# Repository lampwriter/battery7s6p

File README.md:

# 7S6P 18650 module: top and bottom bus boards (v1)

KiCad 9.0.2. The boards are generated by `gen.py` (pcbnew API). `build.sh` regenerates them, fills the zones, runs DRC and renders. `export.sh` writes the JLCPCB outputs to `fab/`.

## v1.1: 1 oz copper variant
`gen.py` reads `CU_OZ` (default 2). `CU_OZ=1 ./build_1oz.sh` builds the 1 oz boards into `top_1oz/` and `bot_1oz/`; `./export_1oz.sh` writes `fab_1oz/`. Order those with **1 oz outer copper** (2 layers, 1.6 mm, ENIG): `fab_1oz/battery7s6p_top_1oz_gerbers.zip` and `fab_1oz/battery7s6p_bot_1oz_gerbers.zip`.

On the 1 oz top board the XT90 moves 23 mm down (y=62 to y=85) so the N7 tail spans rows 0–3 and the neck can carry the current. Cell fuses are 2.0 mm wide on 1 oz (v1 is 1.0 mm on 2 oz), the same copper cross-section and the same blow current. Balance-tap fuses widen from 0.25 mm to 0.45 mm. Every high-current path stays at about 9 C rise or under at 30 A (`fuse_calc_1oz.txt`; the XT90 pad wrap is the warmest, about 9.4 C). The v1 2 oz boards and `fab/` outputs are unchanged.

## v1.2: pressure-contact clamp design
`gen.py` reads `V12` (default off). `V12=1 ./build_v12.sh` builds the boards into `top_v12/` and `bot_v12/`; `./export_v12.sh` writes `fab_v12/`. Order those with **1 oz copper, ENIG, 0.8 mm**: `fab_v12/battery7s6p_top_v12_gerbers.zip` and `fab_v12/battery7s6p_bot_v12_gerbers.zip`. v1 and v1.1 stay selectable (`V12` defaults off), and their gerber zips are unchanged.

Cells stand proud of lipless HDPE holders. The 0.8 mm board has routed slots that make one flexible island per cell, joined by 10 mm bridges, so a short cell can deflect on its own. The stack at each end is a backing plate, **1/8 in silicone foam (Rogers BISCO HT-800)**, then the PCB. Twelve M4 rods sit in equal-length spacer tubes, which set the foam compression at about **25 N per cell**.

`fab_v12/battery7s6p_v12_drill_template.dxf` (and the matching SVG) is the drill template for the holders and plates. Sort cells to **±0.1 mm**. Fit **Kapton rings** on every + end. On the first build, verify **under 15 mV per contact at 5 A**. Details are in `contact_design_v12.txt` and `calc_v12.txt`.

## Arrangement
- 7 columns (series groups G1 to G7) by 6 rows (6 parallel cells per group). Pitch is 20.25 mm and the cell array is 141.75 x 121.5 mm. Each board is 182.75 x 134.5 mm, which includes a 35 mm connector tab.
- Cell orientation alternates by column. Odd groups have + up and even groups have - up.
- Nodes N0 (pack -) to N7 (pack +):
  - The top board busses N1 (G1+/G2-), N3 (G3+/G4-), N5 (G5+/G6-) and N7 (G7+, pack +).
  - The bottom board busses N0 (G1-, pack -), N2, N4 and N6.
- Each board's cell side is its **B (bottom) layer**, and the connectors sit on the outer F side. The bottom board is designed as seen from below, so it's mirrored and its tab ends up under the G1 end.
- Because 7S is odd, pack - (N0) is on the bottom board and pack + is on the top board. N0 reaches the top board's XT90 through one **10 AWG jumper with crimped M5 ring lugs** (about 250 mm) between LUG1 on each board. Bolted, no solder.
- Bottom taps N0, N2, N4 and N6 reach the top board through a **4-pin JST-XH female-female straight cable** (bottom J1 to top J3).

## Holder
This design uses the common square interlocking 18650 bracket: 20.25 mm centre pitch, 18.3/18.5 mm bore, 21.7 mm single cell, about 9 mm thick, ABS+PC V0. It's sold as 1P/2P/3P snap-together pieces (source: chinabatterymachine.com/tmaxcn.com spec table). Buy the **20.25 mm pitch** version, not the 19.0, 19.2 or 19.5 mm variants.

## Mounting
- Ten M3 holes (3.2 mm) at interstitial points between cells, mirror-symmetric so the top and bottom boards line up. Clamp the stack with M3 threaded rod through the holder's corner gaps.
- Two more M3 holes in the tab.
- Check the actual holder before ordering. If its corner gaps can't pass M3 rod, move the holes in `gen.py`.

## Cell contacts (no welding, no solder on cells)
- Positive end: a 6 mm ENIG pad on the cell side, with 6 vias in the pad to the outer layer. Only that pad is positive copper on the cell side. Nothing else on the cell side is copper within the 18.5 mm cell circle, so the bare can shoulder can't short.
- Negative end: a 12 mm ENIG pad, solid into a cell-side pour. That pour exists only under negative-end columns, where the cans are the same net.
- Solder mask covers everything except the contact pads.
- **Fit a fish-paper insulating ring on every + end.** It's marked on the silkscreen.
- Order with **ENIG**, and with **via-in-pad (epoxy filled and capped)** if you want flat + pads.
- Contact pressure comes from clamping the two boards against the holder stack.
- A fully placed SMD contact from JLCPCB/LCSC wasn't found in time. The candidates are MYOUNG MY-18650-04-J (+, C19184125) and MY-18650-05-J (-, C19184124), but their current rating, footprint and SMT suitability are unverified. They're not in the BOM.

## Fusing (one fuse per cell, at its + end)
- Each + island connects to the outer bus pour through a **1.0 mm x about 3.5 mm** 2 oz trace, inside a 6.5 mm no-pour circle.
- Numbers from `fuse_calc.py` / `fuse_calc.txt`:
  - IPC-2221 (external layer, 2 oz): 5.4 A at 20 C rise and 7.3 A at 40 C rise. Normal duty is 30 A / 6 = 5 A per cell.
  - Onderdonk (adiabatic melt): about 20 A in 1 s, 64 A in 100 ms and 200 A in 10 ms.
  - An internally shorted cell is fed by its 5 neighbours (well over 100 A), so the link should open in milliseconds.
- Onderdonk ignores heat sinking. The short link and the mask make the real blow current higher, so bench-test one board with a current source before trusting it.
- Negative ends are not fused (one fuse per cell is enough). Change `FUSE_W` in `gen.py` to retune.

## Bus (30 A)
- 2 oz copper.
- Outer-layer pours span the whole node width (40 mm or more), and the cell-side pours are added under the negative columns.
- Stitching vias (0.5/0.9 mm) sit only in negative-end columns, so there's no positive copper on the cell side near the cans.
- The tab pours are on both layers and carry the XT90 current.

## Connectors (JLCPCB THT assembly, see `fab/*BOM*`, `fab/*CPL*`)
| Ref | Part | LCSC |
|---|---|---|
| Top J1 | AMASS XT90PW-M PCB male, right angle (pad 1 = PACK+ N7, pad 2 = PACK- N0) | C3040689 |
| Top J2 | JST B8B-XH-A balance: pin 1 = N0 (0 V), pin 2 = N1 ... pin 8 = N7 (7S+) | C157972 |
| Top J3 / Bottom J1 | JST B4B-XH-A, inter-board tap link N0/N2/N4/N6 | C144395 |
- Every balance tap has a 0.25 mm x 3 mm fuse link. That's about 2 A continuous, and it melts at about 16 A in 100 ms.
- On the top board, J2/J3 pin 1 is the separate net `N0_SENSE`. It's connected to N0 only through the bottom board and cable, which is intentional.

## Fab settings
- 2 layers, 1.6 mm, **2 oz outer copper**, ENIG, any mask colour.
- Upload `battery7s6p_top_gerbers.zip` and `battery7s6p_bot_gerbers.zip` as separate orders.
- The CPL coordinates are footprint origins (pin 1), not centroids. Check the part placement and rotation in JLCPCB's assembly preview.

## DRC
Rules: 0.2 mm track and clearance, 0.3 mm hole, 0.6 mm via, 0.4 mm copper-to-edge. Zone clearance is 0.5 mm. Results:
- 0 errors and 0 unconnected items.
- Remaining warnings are harmless:
  - "footprint library battery7s6p not configured": the cell contacts are script-generated footprints.
  - XT90 silk overhangs the edge, because the connector intentionally overhangs by 2.6 mm.

## Open items
- Check XT90 polarity against the housing. The XT90-S anti-spark version is a cable connector, so put the XT90-S on the mating harness side. The PCB part is the standard XT90PW.
- Revolectrix balance pin order is assumed to be standard JST-XH (pin 1 = pack -). Check it against your adapter board.
- There's no BMS or balancer in v1. Real-world fuse-blow testing is still to do.

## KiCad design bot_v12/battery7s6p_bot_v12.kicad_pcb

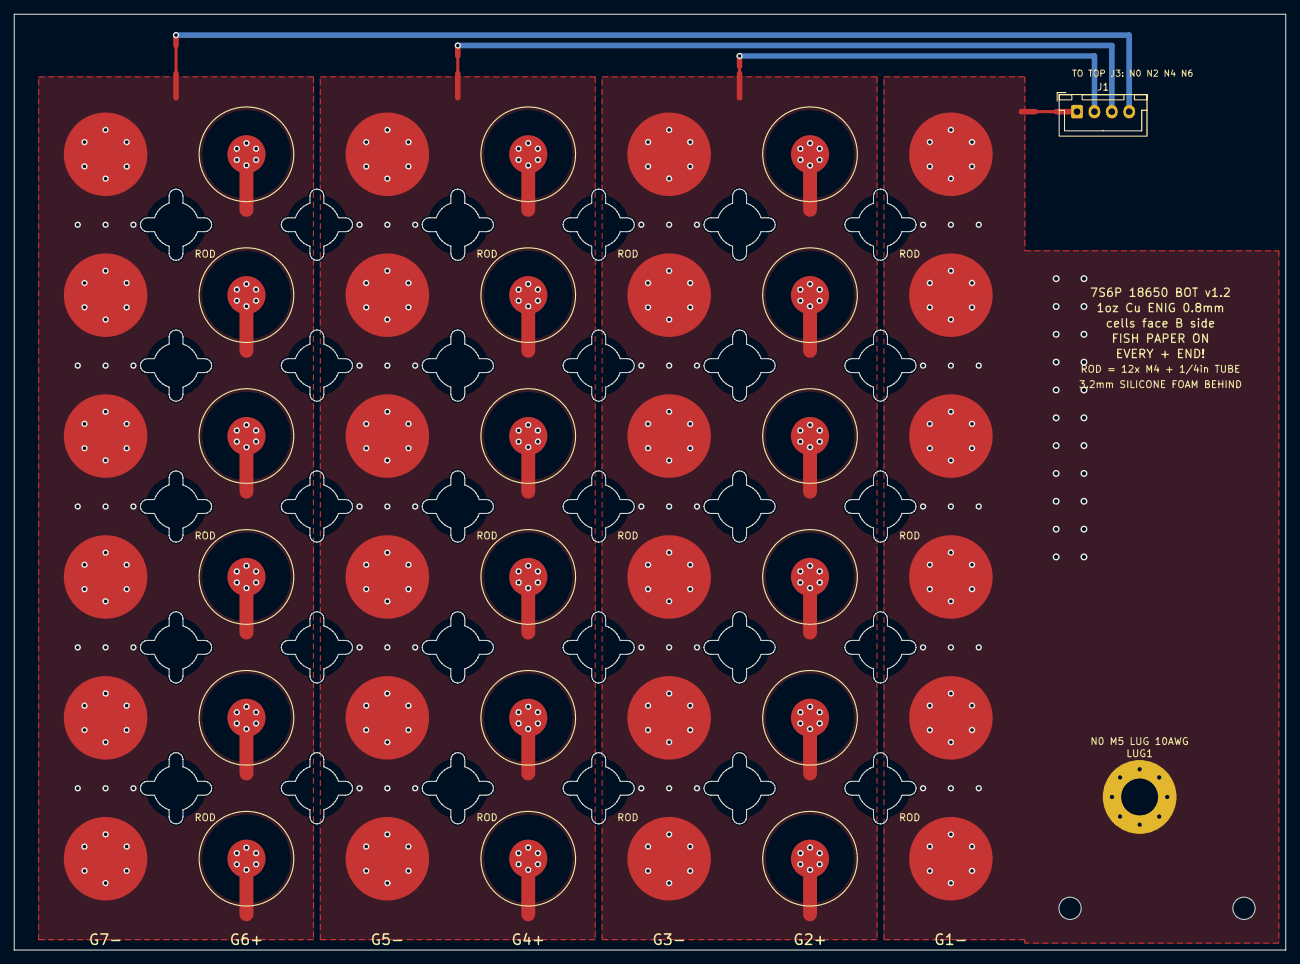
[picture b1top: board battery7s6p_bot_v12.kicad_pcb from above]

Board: 2 copper layers, 182.8 x 134.5 mm, 46 parts (0 on the bottom side), 4 nets.

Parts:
C1_1, C1_2, C1_3, C1_4, C1_5, C1_6, C3_1, C3_2, C3_3, C3_4, C3_5, C3_6, C5_1, C5_2, C5_3, C5_4, C5_5, C5_6, C7_1, C7_2, C7_3, C7_4, C7_5, C7_6: 18650_NEG; CELL_NEG_CONTACT
C2_1, C2_2, C2_3, C2_4, C2_5, C2_6, C4_1, C4_2, C4_3, C4_4, C4_5, C4_6, C6_1, C6_2, C6_3, C6_4, C6_5, C6_6: 18650_POS; CELL_POS_CONTACT
HT0, HT1: MountingHole_3.2mm_M3
J1: B4B-XH-A to TOP; JST_XH_B4B-XH-A_1x04_P2.50mm_Vertical
LUG1: N0 M5 LUG; MountingHole_5.3mm_M5_Pad_Via

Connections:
N0: C1_1.1, C1_2.1, C1_3.1, C1_4.1, C1_5.1, C1_6.1, J1.1, LUG1.1
N2: C2_1.1, C2_2.1, C2_3.1, C2_4.1, C2_5.1, C2_6.1, C3_1.1, C3_2.1, C3_3.1, C3_4.1, C3_5.1, C3_6.1, J1.2
N4: C4_1.1, C4_2.1, C4_3.1, C4_4.1, C4_5.1, C4_6.1, C5_1.1, C5_2.1, C5_3.1, C5_4.1, C5_5.1, C5_6.1, J1.3
N6: C6_1.1, C6_2.1, C6_3.1, C6_4.1, C6_5.1, C6_6.1, C7_1.1, C7_2.1, C7_3.1, C7_4.1, C7_5.1, C7_6.1, J1.4

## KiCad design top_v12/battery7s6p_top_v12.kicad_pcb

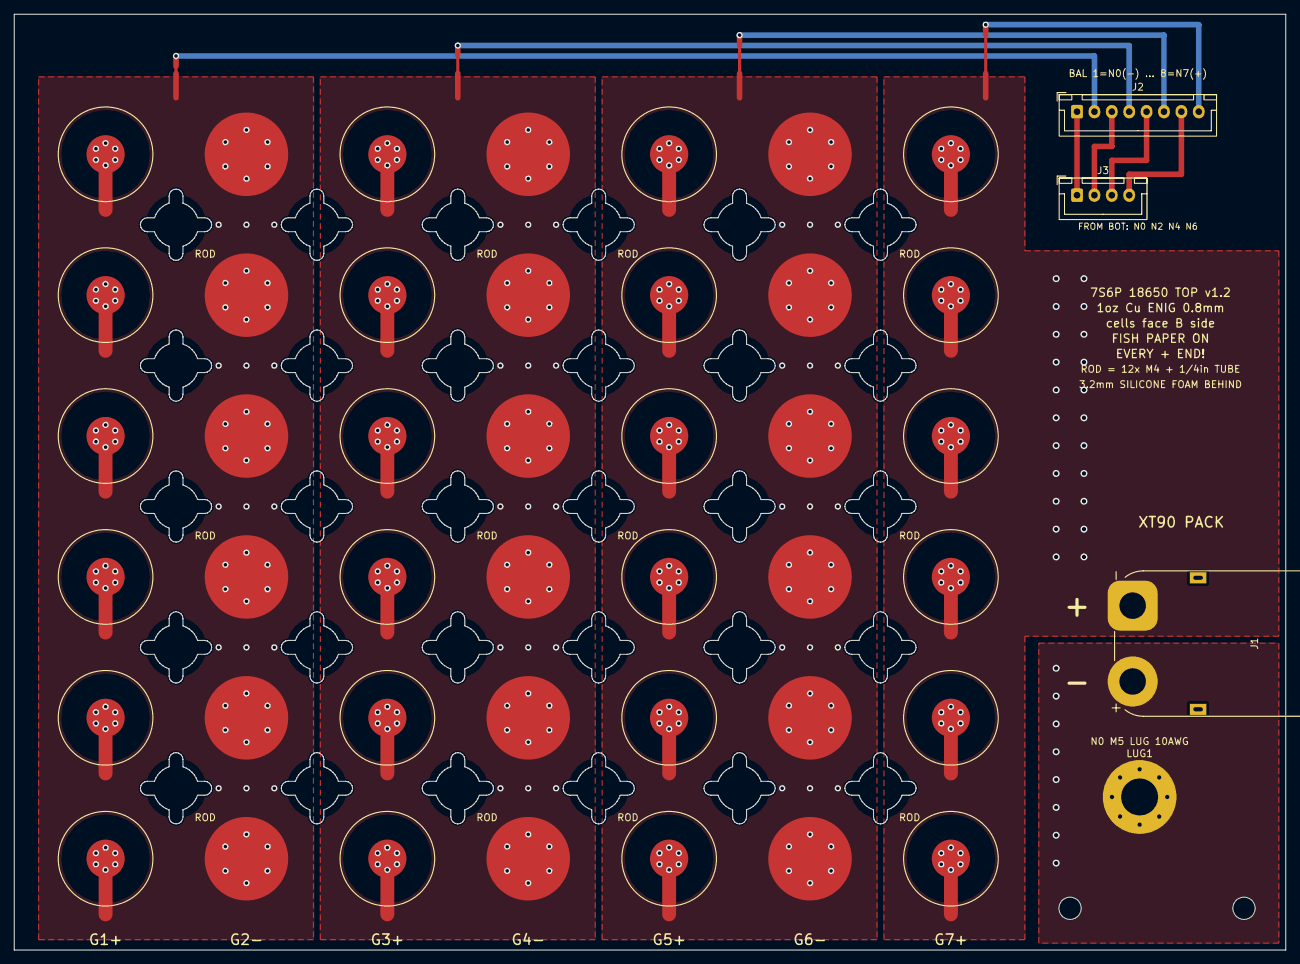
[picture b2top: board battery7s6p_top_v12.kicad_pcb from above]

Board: 2 copper layers, 182.8 x 134.5 mm, 48 parts (0 on the bottom side), 9 nets.

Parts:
C1_1, C1_2, C1_3, C1_4, C1_5, C1_6, C3_1, C3_2, C3_3, C3_4, C3_5, C3_6, C5_1, C5_2, C5_3, C5_4, C5_5, C5_6, C7_1, C7_2, C7_3, C7_4, C7_5, C7_6: 18650_POS; CELL_POS_CONTACT
C2_1, C2_2, C2_3, C2_4, C2_5, C2_6, C4_1, C4_2, C4_3, C4_4, C4_5, C4_6, C6_1, C6_2, C6_3, C6_4, C6_5, C6_6: 18650_NEG; CELL_NEG_CONTACT
HT0, HT1: MountingHole_3.2mm_M3
J1: XT90PW-M; AMASS_XT90PW-M_1x02_P10.90mm_Horizontal
J2: B8B-XH-A BAL; JST_XH_B8B-XH-A_1x08_P2.50mm_Vertical
J3: B4B-XH-A from BOT; JST_XH_B4B-XH-A_1x04_P2.50mm_Vertical
LUG1: N0 M5 LUG; MountingHole_5.3mm_M5_Pad_Via

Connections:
N0: J1.2, LUG1.1
N0_SENSE: J2.1, J3.1
N1: C1_1.1, C1_2.1, C1_3.1, C1_4.1, C1_5.1, C1_6.1, C2_1.1, C2_2.1, C2_3.1, C2_4.1, C2_5.1, C2_6.1, J2.2
N2: J2.3, J3.2
N3: C3_1.1, C3_2.1, C3_3.1, C3_4.1, C3_5.1, C3_6.1, C4_1.1, C4_2.1, C4_3.1, C4_4.1, C4_5.1, C4_6.1, J2.4
N4: J2.5, J3.3
N5: C5_1.1, C5_2.1, C5_3.1, C5_4.1, C5_5.1, C5_6.1, C6_1.1, C6_2.1, C6_3.1, C6_4.1, C6_5.1, C6_6.1, J2.6
N6: J2.7, J3.4
N7: C7_1.1, C7_2.1, C7_3.1, C7_4.1, C7_5.1, C7_6.1, J1.1, J2.8
